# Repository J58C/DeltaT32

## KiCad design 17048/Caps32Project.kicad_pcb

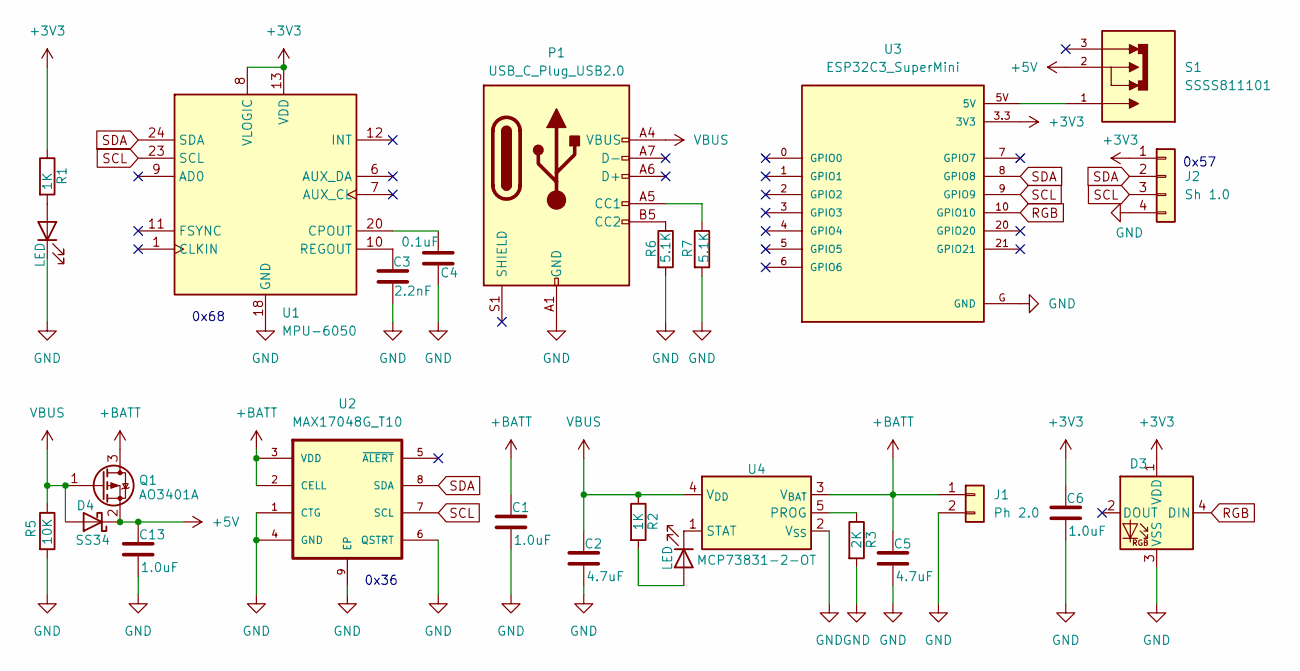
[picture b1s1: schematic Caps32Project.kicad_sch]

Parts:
C1, C6, C13: 1.0uF; C_0402_1005Metric_Pad0.74x0.62mm_HandSolder
C2, C5: 4.7uF; C_0402_1005Metric_Pad0.74x0.62mm_HandSolder
C3: 2.2nF; C_0402_1005Metric_Pad0.74x0.62mm_HandSolder
C4: 0.1uF; C_0402_1005Metric_Pad0.74x0.62mm_HandSolder
D1, D2: LED; LED_0402_1005Metric_Pad0.77x0.64mm_HandSolder
D3: WS2812B; LED_WS2812B_PLCC4_5.0x5.0mm_P3.2mm
D4: SS34; D_SMA
J1: Ph 2.0; JST_PH_S2B-PH-SM4-TB_1x02-1MP_P2.00mm_Horizontal
J2: Sh 1.0; JST_SH_SM04B-SRSS-TB_1x04-1MP_P1.00mm_Horizontal
P1: USB_C_Plug_USB2.0; USB_C_Receptacle_XKB_U262-16XN-4BVC11
Q1: AO3401A; SOT-23
R1, R2: 1K; R_0402_1005Metric_Pad0.72x0.64mm_HandSolder
R3: 2K; R_0402_1005Metric_Pad0.72x0.64mm_HandSolder
R5: 10K; R_0402_1005Metric_Pad0.72x0.64mm_HandSolder
R6, R7: 5.1K; R_0402_1005Metric_Pad0.72x0.64mm_HandSolder
S1: SSSS811101; SW_SSSS811101; PARTREV N/A
U1: MPU-6050; InvenSense_QFN-24_4x4mm_P0.5mm
U2: MAX17048G_T10; SON50P200X200X80-9N
U3: ESP32C3_SuperMini; ESP32C3_Supermini_SMD
U4: MCP73831-2-OT; SOT-23-5

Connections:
+3V3: C6.1, D3.1 (VDD), J2.1, R1.1, U1.8 (VLOGIC), U1.13 (VDD), U3.3.3 (3V3)
+5V: C13.1, D4.1 (K), Q1.2 (S), S1.2
+BATT: C1.1, C5.1, J1.1, Q1.3 (D), U2.2 (CELL), U2.3 (VDD), U4.3 (V_{BAT})
GND: C1.2, C2.2, C3.1, C4.2, C5.2, C6.2, C13.2, D1.1 (K), D3.3 (VSS), J1.2, J2.4, P1.A1 (GND), P1.A12 (GND), P1.B1 (GND), P1.B12 (GND), R3.2, R5.2, R6.2, R7.2, U1.18 (GND), U2.1 (CTG), U2.4 (GND), U2.6 (QSTRT), U2.9 (EP), U3.G (GND), U4.2 (V_{SS})
unnamed: D1.2 (A), R1.2
unnamed: D2.2 (A), R2.2
unnamed: D2.1 (K), U4.1 (STAT)
unnamed: P1.A5 (CC1), R7.1
unnamed: P1.B5 (CC2), R6.1
unnamed: S1.1, U3.5V
unnamed: C4.1, U1.20 (CPOUT)
unnamed: C3.2, U1.10 (REGOUT)
unnamed: R3.1, U4.5 (PROG)
RGB: D3.4 (DIN), U3.10 (GPIO10)
SCL: J2.3, U1.23 (SCL), U2.7 (SCL), U3.9 (GPIO9)
SDA: J2.2, U1.24 (SDA), U2.8 (SDA), U3.8 (GPIO8)
VBUS: C2.1, D4.2 (A), P1.A4 (VBUS), P1.A9 (VBUS), P1.B4 (VBUS), P1.B9 (VBUS), Q1.1 (G), R2.1, R5.1, U4.4 (V_{DD})

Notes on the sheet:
0x57
0x36
0x68

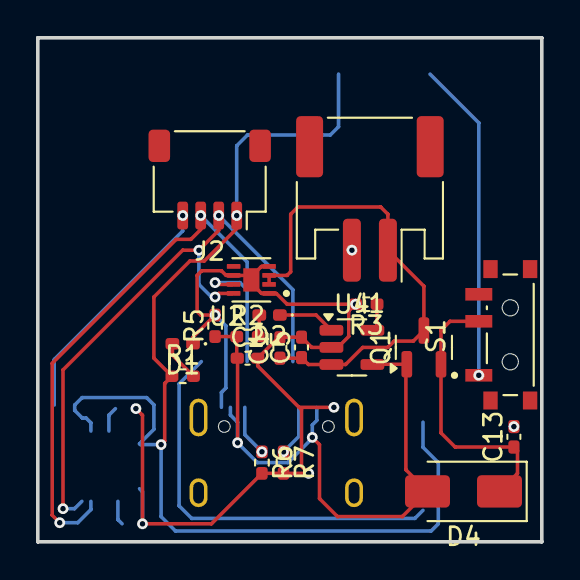
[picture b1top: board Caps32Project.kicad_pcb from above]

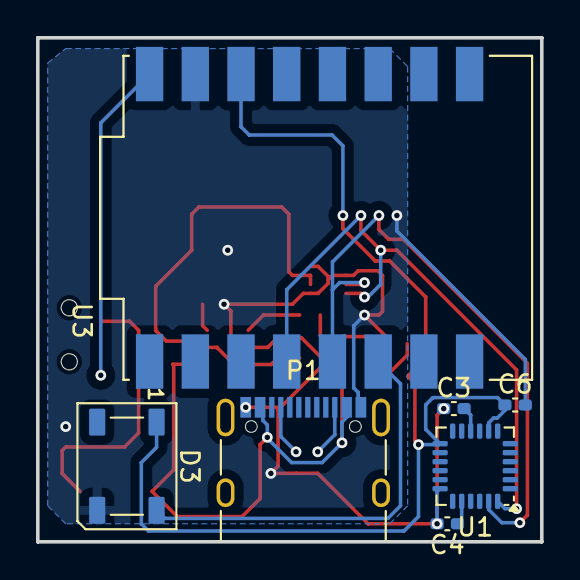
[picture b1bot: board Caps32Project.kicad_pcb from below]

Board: 2 copper layers, 28.0 x 28.0 mm, 26 parts (7 on the bottom side), 17 nets.

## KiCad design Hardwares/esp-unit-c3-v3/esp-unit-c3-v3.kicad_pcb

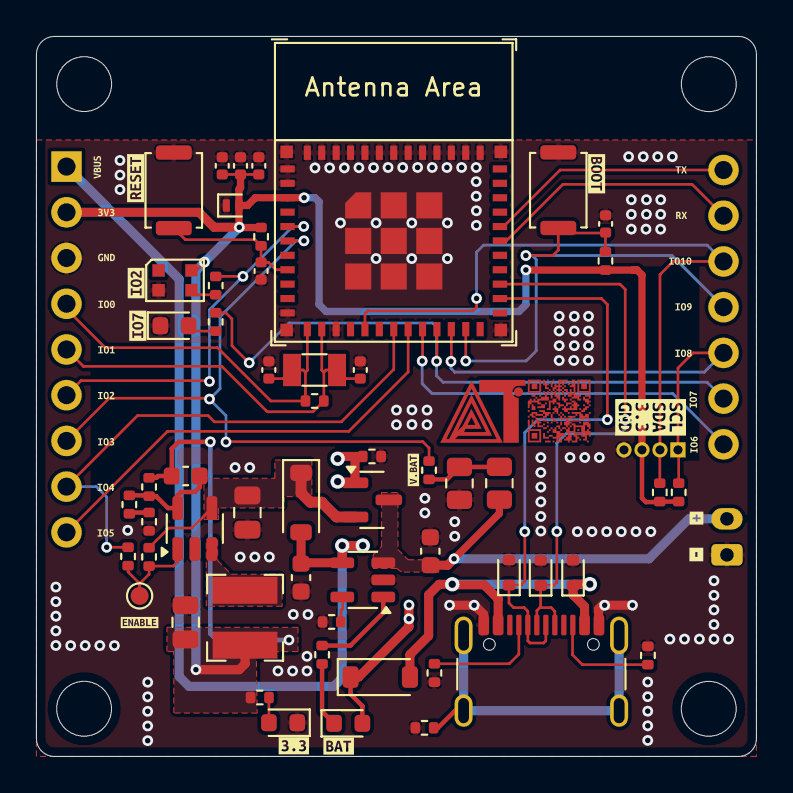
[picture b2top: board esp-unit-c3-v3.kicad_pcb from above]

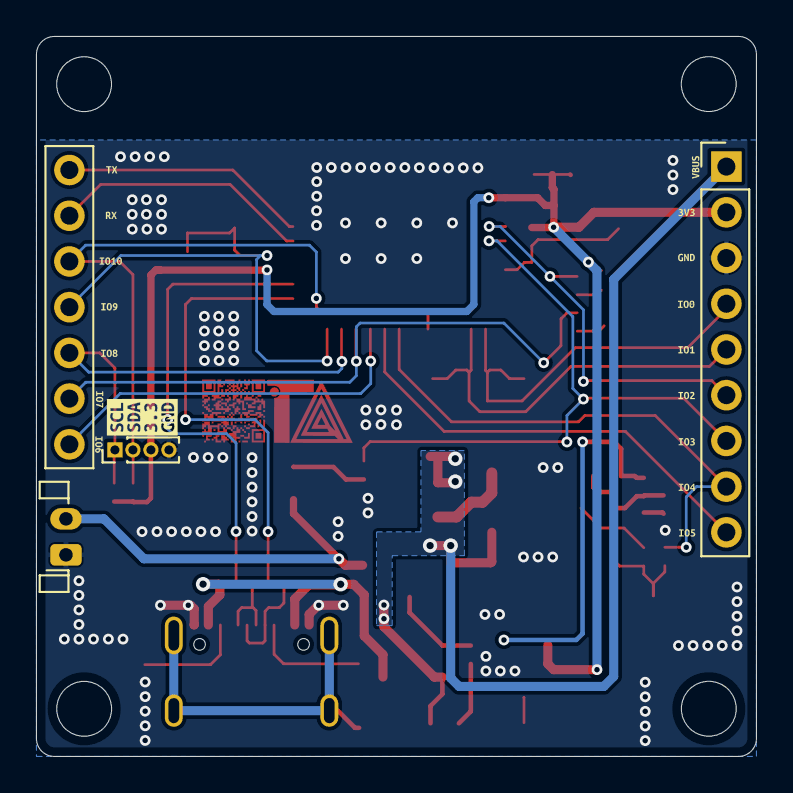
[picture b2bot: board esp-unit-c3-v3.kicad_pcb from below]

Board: 2 copper layers, 40.0 x 40.0 mm, 101 parts (19 on the bottom side), 36 nets.

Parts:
C1: 10nF 10V; C_0402_1005Metric
C2: 100nF 10V; C_0402_1005Metric
C3, C4: 1uF 16V; C_0402_1005Metric
C5, C6: DNP; C_0402_1005Metric
C7, C9: 4.7uF 16V; C_0603_1608Metric
C8: 1nF 10V; C_0402_1005Metric
C10, C12: 10uF 16V; C_0805_2012Metric
C11: 22pF 50V; C_0603_1608Metric
D1: WS2812B; LED_WS2812B-2020_PLCC4_2.0x2.0mm
D2: LESD8D3.3CAT5G; D_SOD-882
D3: WHITE LED; LED_0603_1608Metric
D4: RED LED; LED_0603_1608Metric
D5, D7: B5819W; D_SOD-123
D6, D8, D9: LESD5D5.0CT1G; D_SOD-523
D10: DNP; LED_0603_1608Metric
J1: Conn_01x04; PinHeader_1x04_P1.00mm_Vertical
J2: JST PH2.0; JST_PH2.0
J3: USB C 16P; USB_C_Receptacle_GCT_USB4105-xx-A_16P_TopMnt_Horizontal
L1: SPH4018H2R2MT (2.2uH 2.2A); L_Bourns-SRN4018
Q1: DMG3415U; SOT-23
R1, R11, R19, R20: 0R; R_0402_1005Metric
R2, R4, R5, R7, R8, R12: 10K; R_0402_1005Metric
R3, R21: 470R; R_0402_1005Metric
R6: DNP; R_0402_1005Metric
R9: 1K; R_0402_1005Metric
R10, R15: 100K; R_0402_1005Metric
R13, R14: 5K1; R_0402_1005Metric
R16: 22K; R_0402_1005Metric
R17: 442K; R_0805_2012Metric
R18: 160K; R_0805_2012Metric
R22: 100; R_0402_1005Metric
SW1: BOOT; SW_Push_SPST_NO_Alps_SKRK
SW2: RESET; SW_Push_SPST_NO_Alps_SKRK
TP1: ENABLE; TestPoint_Pad_D1.0mm
U1: ESP32-C3-MINI-1
U2: Delta Board 2; Delta_Board-2
U3: MCP73831T-2ACI/OT; SOT-23-5
U4: SY8088; SOT-23-5
Y1: 32.768Hz; Crystal_SMD_3215-2Pin_3.2x1.5mm
kibuzzard-680CD9B9: G***; kibuzzard-680CD9B9
kibuzzard-680CD9CB: G***; kibuzzard-680CD9CB
kibuzzard-680CDA1E: G***; kibuzzard-680CDA1E
kibuzzard-680CDA08: G***; kibuzzard-680CDA08
kibuzzard-680CDA64: G***; kibuzzard-680CDA64
kibuzzard-680CDBCC: G***; kibuzzard-680CDBCC
kibuzzard-680CDBED: G***; kibuzzard-680CDBED
kibuzzard-680CDFA2: G***; kibuzzard-680CDFA2
kibuzzard-680CFCF0, kibuzzard-680CFCF0#2: G***; kibuzzard-680CFCF0
kibuzzard-680CFD7F, kibuzzard-680CFD7F#2: G***; kibuzzard-680CFD7F
kibuzzard-680CFD12, kibuzzard-680CFD12#2: G***; kibuzzard-680CFD12
kibuzzard-680CFD73, kibuzzard-680CFD73#2: G***; kibuzzard-680CFD73
kibuzzard-680CFDA8, kibuzzard-680CFDA8#2: G***; kibuzzard-680CFDA8
kibuzzard-680CFDBB, kibuzzard-680CFDBB#2: G***; kibuzzard-680CFDBB
kibuzzard-680CFDCF, kibuzzard-680CFDCF#2: G***; kibuzzard-680CFDCF
kibuzzard-680CFDE4, kibuzzard-680CFDE4#2: G***; kibuzzard-680CFDE4
kibuzzard-680CFDFB, kibuzzard-680CFDFB#2: G***; kibuzzard-680CFDFB
kibuzzard-680CFE08, kibuzzard-680CFE08#2: G***; kibuzzard-680CFE08
kibuzzard-680CFF32: G***; kibuzzard-680CFF32
kibuzzard-6816DD82, kibuzzard-6816DD82#2: G***; kibuzzard-6816DD82
kibuzzard-6816DDEA, kibuzzard-6816DDEA#2: G***; kibuzzard-6816DDEA
kibuzzard-6816DDFD, kibuzzard-6816DDFD#2: G***; kibuzzard-6816DDFD
kibuzzard-6816DE5B, kibuzzard-6816DE5B#2: G***; kibuzzard-6816DE5B
kibuzzard-6816DE78, kibuzzard-6816DE78#2: G***; kibuzzard-6816DE78
kibuzzard-6816DE97, kibuzzard-6816DE97#2: G***; kibuzzard-6816DE97
kibuzzard-6816EC1C, kibuzzard-6816EC1C#2: G***; kibuzzard-6816EC1C
kibuzzard-68198D94: G***; kibuzzard-68198D94

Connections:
+3V3: C1.2, C2.2, C3.2, C11.1, C12.1, D1.4 (VDD), D2.2 (A2), J1.3, L1.2, R2.2, R4.2, R5.1, R8.2, R15.2, R21.1, U1.3 (3V3), U2.2 (3V3)
+5V: C10.1, D5.1 (K), Q1.2 (S), R12.2, U4.4 (IN)
+BATT: C9.1, J2.2, Q1.3 (D), R17.2, U3.3 (VBAT)
/Buck_Coil: L1.1, U4.3 (LX)
CHIP_PU: C4.1, R5.2, SW2.1, U1.8 (EN/CHIP_PU)
GND: C1.1, C2.1, C3.1, C4.2, C5.2, C6.2, C7.1, C8.2, C9.2, C10.2, C12.2, D1.2 (VSS), D2.1 (A1), D3.1 (K), D6.2 (A2), D8.2 (A2), D9.2 (A2), D10.1 (K), J1.4, J2.1, J3.A1 (GND), J3.A12 (GND), J3.B1 (GND), J3.B12 (GND), R7.1, R10.1, R11.1, R13.1, R14.1, R16.1, R18.1, SW1.2, SW2.2, U1.1 (GND), U1.2 (GND), U1.11 (GND), U1.14 (GND), U1.36 (GND), U1.37 (GND), U1.38 (GND), U1.39 (GND), U1.40 (GND), U1.41 (GND), U1.42 (GND), U1.43 (GND), U1.44 (GND), U1.45 (GND), U1.46 (GND), U1.47 (GND), U1.48 (GND), U1.49 (GND), U1.50 (GND), U1.51 (GND), U1.52 (GND), U1.53 (GND), U2.3 (GND), U3.2 (VSS), U4.2 (GND)
IO0: C5.1, R6.1, U1.12 (GPIO0/ADC1_CH0/XTAL_32K_P), U2.4 (A0/GPIO0), Y1.1
IO1: C6.1, R6.2, U1.13 (GPIO1/ADC1_CH1/XTAL_32K_N), U2.5 (A1/GPIO1), Y1.2
IO2: R1.1, U1.5 (GPIO2/ADC1_CH2), U2.6 (A2/GPIO2)
IO3: R19.1, U1.6 (GPIO3/ADC1_CH3), U2.7 (A3/GPIO3)
IO4: R20.1, U1.18 (GPIO4/ADC1_CH4), U2.8 (A4/GPIO4)
IO5: U1.19 (GPIO5/ADC2_CH0), U2.9 (A5/GPIO5)
IO6: U1.20 (GPIO6), U2.10 (GPIO6)
IO7: R3.1, U1.21 (GPIO7), U2.11 (GPIO7)
IO8_SCL: J1.1, R2.1, U1.22 (GPIO8), U2.12 (SCL/GPIO8)
IO9_BOOT: C8.1, R8.1, SW1.1, U1.23 (GPIO9), U2.13 (BOOT/GPIO9)
IO10_SDA: J1.2, R4.1, U1.16 (GPIO10), U2.14 (SDA/GPIO10)
IO20_RX: U1.30 (GPIO20/U0RXD), U2.15 (TXD/GPIO21)
IO21_TX: U1.31 (GPIO21/U0TXD), U2.16 (RXD/GPIO20)
unnamed: D1.3 (DIN), R1.2
unnamed: D3.2 (A), R3.2
unnamed: D4.1 (K), R9.2
unnamed: D7.2 (A), D8.1 (A1), J3.A4 (VBUS), J3.A9 (VBUS), J3.B4 (VBUS), J3.B9 (VBUS)
unnamed: D10.2 (A), R21.2
unnamed: J3.A5 (CC1), R13.2
unnamed: J3.B5 (CC2), R14.2
unnamed: J3.S1 (SHIELD), R11.2
unnamed: R16.2, R22.2
unnamed: R17.1, R18.2, R19.2
unnamed: R7.2, U3.5 (PROG)
unnamed: R9.1, U3.1 (STAT)
unnamed: R12.1, R20.2, TP1.1, U4.1 (EN)
unnamed: C11.2, R15.1, R22.1, U4.5 (FB)
USB_D+: D6.1 (A1), J3.A6 (D+), J3.B6 (D+), U1.27 (GPIO19/USB_D+)
USB_D-: D9.1 (A1), J3.A7 (D-), J3.B7 (D-), U1.26 (GPIO18/USB_D-)
VBUS: C7.2, D4.2 (A), D5.2 (A), D7.1 (K), Q1.1 (G), R10.2, U2.1 (VBUS), U3.4 (VDD)

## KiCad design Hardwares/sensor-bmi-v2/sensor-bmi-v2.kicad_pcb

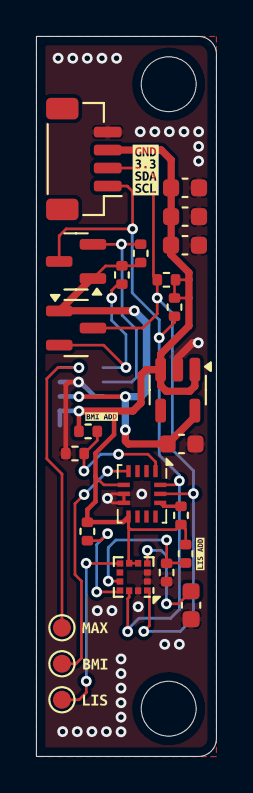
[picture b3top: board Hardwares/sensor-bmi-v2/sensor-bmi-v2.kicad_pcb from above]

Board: 2 copper layers, 10.0 x 40.0 mm, 31 parts (1 on the bottom side), 15 nets.

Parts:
C41: 1uF 16V; C_0603_1608Metric
C42: 2.2uF 16V; C_0603_1608Metric
C43, C44, C45: 100nF 10V; C_0603_1608Metric
J41: JST SH1.0; JST_SH_BM04B-SRSS-TB_1x04-1MP_P1.00mm_Vertical
Q41, Q42: BSS138; SOT-23
R41, R42, R43, R44, R45, R48, R49, R51: 10K; R_0402_1005Metric
R47, R50: DNP; R_0402_1005Metric
TP41: MAX_INT; TestPoint_Pad_D1.0mm
TP42: LIS_INT; TestPoint_Pad_D1.0mm
TP43: BMI_INT; TestPoint_Pad_D1.0mm
U41: LN1134A182MR-G; SOT-23-5
U42: MAX30102; Maxim_OLGA-14_3.3x5.6mm_P0.8mm
U44: BMI270; Bosch_LGA-14_3x2.5mm_P0.5mm
U45: LIS3MDL; LGA-12_2x2mm_P0.5mm
kibuzzard-680F6A2F: G***; kibuzzard-680F6A2F
kibuzzard-680F6A44: G***; kibuzzard-680F6A44
kibuzzard-680F69F9: G***; kibuzzard-680F69F9
kibuzzard-6818BCEF: G***; kibuzzard-6818BCEF
kibuzzard-6818BD0F: G***; kibuzzard-6818BD0F
kibuzzard-6817376F: G***; kibuzzard-6817376F

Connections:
+1V8: C42.1, Q41.1 (G), Q42.1 (G), R41.1, R42.1, U41.5 (VOUT), U42.11 (VDD)
+3V3: C41.1, C44.1, C45.1, J41.3, R43.1, R44.2, R45.2, R47.1, R49.1, R50.1, U41.1 (VIN), U41.3 (EN), U42.9 (VLED+), U42.10 (VLED+), U44.5 (VDDIO), U44.8 (VDD), U45.5 (Vdd), U45.6 (Vdd_IO)
GND: C41.2, C42.2, C43.2, C44.2, C45.2, J41.4, R48.2, R51.2, U41.2 (GND), U42.4 (PGND), U42.12 (GND), U44.6 (GNDIO), U44.7 (GND), U45.2 (GND), U45.3 (GND), U45.12 (GND)
unnamed: TP41.1, U42.13 (~INT)
unnamed: R49.2, U44.12 (CSB)
unnamed: TP43.1, U44.4 (INT1)
unnamed: R47.2, R48.1, U44.1 (SDO)
unnamed: C43.1, U45.4 (C1)
unnamed: TP42.1, U45.7 (INT)
unnamed: R50.2, R51.1, U45.9 (SDO/SA1)
unnamed: R43.2, U45.10 (~CS)
SCL: J41.2, Q41.3 (D), R45.1, U44.13 (SCx), U45.1 (SCL/SPC)
SCL_1V8: Q41.2 (S), R42.2, U42.2 (SCL)
SDA: J41.1, Q42.3 (D), R44.1, U44.14 (SDx), U45.11 (SDA/SDI/SDO)
SDA_1V8: Q42.2 (S), R41.2, U42.3 (SDA)

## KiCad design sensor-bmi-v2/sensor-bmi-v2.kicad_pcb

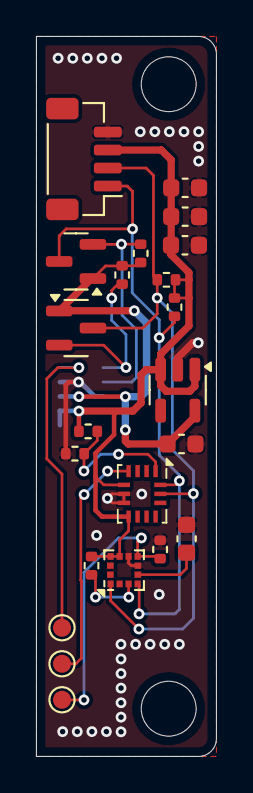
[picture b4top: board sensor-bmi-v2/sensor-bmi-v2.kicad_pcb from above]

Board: 2 copper layers, 10.0 x 40.0 mm, 23 parts (1 on the bottom side), 13 nets.

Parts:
C1: 1uF 16V; C_0603_1608Metric
C2: 2.2uF 16V; C_0603_1608Metric
C3, C4, C5: 100nF 16V; C_0603_1608Metric
J1: JST SH1.0; JST_SH_BM04B-SRSS-TB_1x04-1MP_P1.00mm_Vertical
Q1, Q2: BSS138; SOT-23
R1, R2, R3, R4, R5, R6, R8: 10K; R_0402_1005Metric
R7: 0R; R_0402_1005Metric
TP1: MAX_INT; TestPoint_Pad_D1.0mm
TP2: LIS_INT; TestPoint_Pad_D1.0mm
TP3: BMI_INT; TestPoint_Pad_D1.0mm
U1: LN1134A182MR-G; SOT-23-5
U2: MAX30102; Maxim_OLGA-14_3.3x5.6mm_P0.8mm
U3: LIS2MDL; LGA-12_2x2mm_P0.5mm
U4: BMI160; Bosch_LGA-14_3x2.5mm_P0.5mm

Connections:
+1V8: C2.1, Q1.1 (G), Q2.1 (G), R1.1, R2.1, U1.5 (VOUT), U2.11 (VDD)
+3V3: C1.1, C4.1, C5.1, J1.3, R3.1, R4.2, R5.2, R7.1, U1.1 (VIN), U1.3 (EN), U2.9 (VLED+), U2.10 (VLED+), U3.9 (Vdd), U3.10 (Vdd_IO), U4.5 (VDDIO), U4.8 (VDD)
GND: C1.2, C2.2, C3.2, C4.2, C5.2, J1.4, R6.2, R8.2, U1.2 (GND), U2.4 (PGND), U2.12 (GND), U3.6 (GND), U3.8 (GND), U4.6 (GNDIO), U4.7 (GND)
unnamed: TP1.1, U2.13 (~INT)
unnamed: C3.1, U3.5 (C1)
unnamed: R6.1, TP2.1, U3.7 (DRDY)
unnamed: R3.2, U3.3 (~CS)
unnamed: TP3.1, U4.4 (INT1)
unnamed: R7.2, R8.1, U4.1 (SDO)
SCL: J1.2, Q1.3 (D), R5.1, U3.1 (SCL/SPC), U4.13 (SCx)
SCL_1V8: Q1.2 (S), R2.2, U2.2 (SCL)
SDA: J1.1, Q2.3 (D), R4.1, U3.4 (SDA/SDI/SDO), U4.14 (SDx)
SDA_1V8: Q2.2 (S), R1.2, U2.3 (SDA)
